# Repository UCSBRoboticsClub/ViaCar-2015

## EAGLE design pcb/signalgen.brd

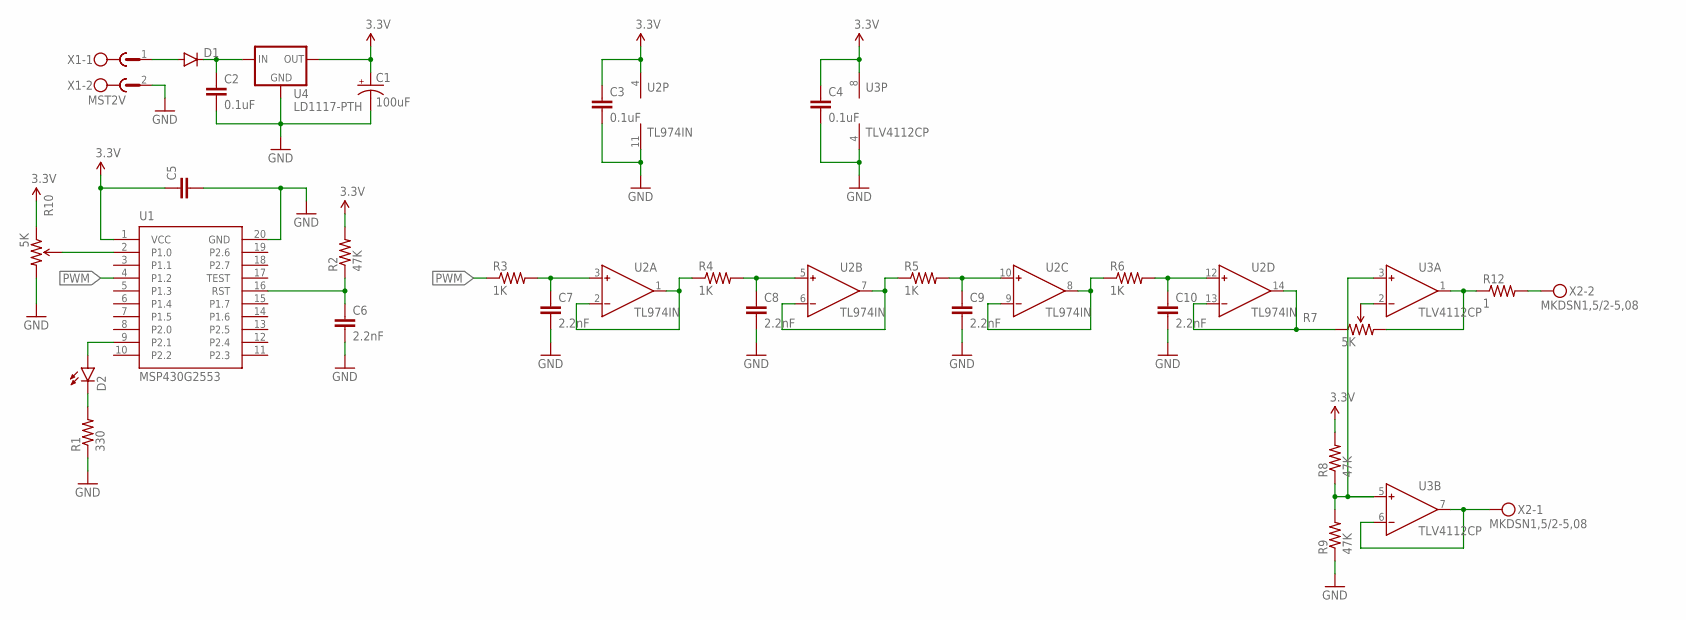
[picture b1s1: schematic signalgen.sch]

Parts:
C1: 100uF; CPOL-RADIAL-100UF-25V
C2, C3, C4: 0.1uF; CAP-PTH-SMALL
C5: CAPPTH; CAP-PTH-SMALL
C6, C7, C8, C9, C10: 2.2nF; CAP-PTH-SMALL
D1: DIODEPTH; DIODE-1N4001
D2: LED-3MM-NO_SILK; LED3MM-NS
R1: 330; AXIAL-0.1
R2, R8, R9: 47K; AXIAL-0.3
R3, R5: 1K; AXIAL-0.1
R4, R6: 1K; AXIAL-0.3
R7, R10: 5K; TRIM_POT_PTH
R12: 1; AXIAL-0.6
U1: MSP430G2553; DIP-20
U2: TL974IN; DIP-14
U3: TLV4112CP; DIP-8
U4: LD1117-PTH; TO-220ABS
X1: MST2V; MSTBV2
X2: MKDSN1,5/2-5,08

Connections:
3.3V: C1.1 (+), C3.1, C4.1, C5.1, R2.P$2 (2), R8.P$2 (2), R10.1 (CCW), U1.1 (VCC), U2.4 (V+), U3.8 (V+), U4.2 (OUT)
GND: C1.2 (-), C2.2, C3.2, C4.2, C5.2, C6.2, C7.2, C8.2, C9.2, C10.2, R1.P$1 (1), R9.P$1 (1), R10.3 (CW), U1.20 (GND), U2.11 (V-), U3.4 (V-), U4.1 (GND), X1.2
unnamed: D1.A, X1.1
unnamed: C2.1, D1.C, U4.3 (IN)
unnamed: D2.K (C), R1.P$2 (2)
unnamed: R4.P$1 (1), U2.1 (OUT), U2.2 (IN-)
unnamed: C7.1, R3.P$2 (2), U2.3 (IN+)
unnamed: R5.P$1 (1), U2.6 (IN-), U2.7 (OUT)
unnamed: C6.1, R2.P$1 (1), U1.16 (RST)
unnamed: U3.6 (IN-), U3.7 (OUT), X2.1
unnamed: C8.1, R4.P$2 (2), U2.5 (IN+)
unnamed: C10.1, R6.P$2 (2), U2.12 (IN+)
unnamed: R12.P$2 (2), X2.2
unnamed: C9.1, R5.P$2 (2), U2.10 (IN+)
unnamed: R6.P$1 (1), U2.8 (OUT), U2.9 (IN-)
unnamed: R7.1 (CCW), U2.13 (IN-), U2.14 (OUT)
unnamed: R8.P$1 (1), R9.P$2 (2), U3.3 (IN+), U3.5 (IN+)
unnamed: R7.3 (CW), R12.P$1 (1), U3.1 (OUT)
unnamed: R10.2 (WIPER), U1.2 (P1.0)
unnamed: R7.2 (WIPER), U3.2 (IN-)
unnamed: D2.A, U1.9 (P2.1)
PWM: R3.P$1 (1), U1.4 (P1.2)

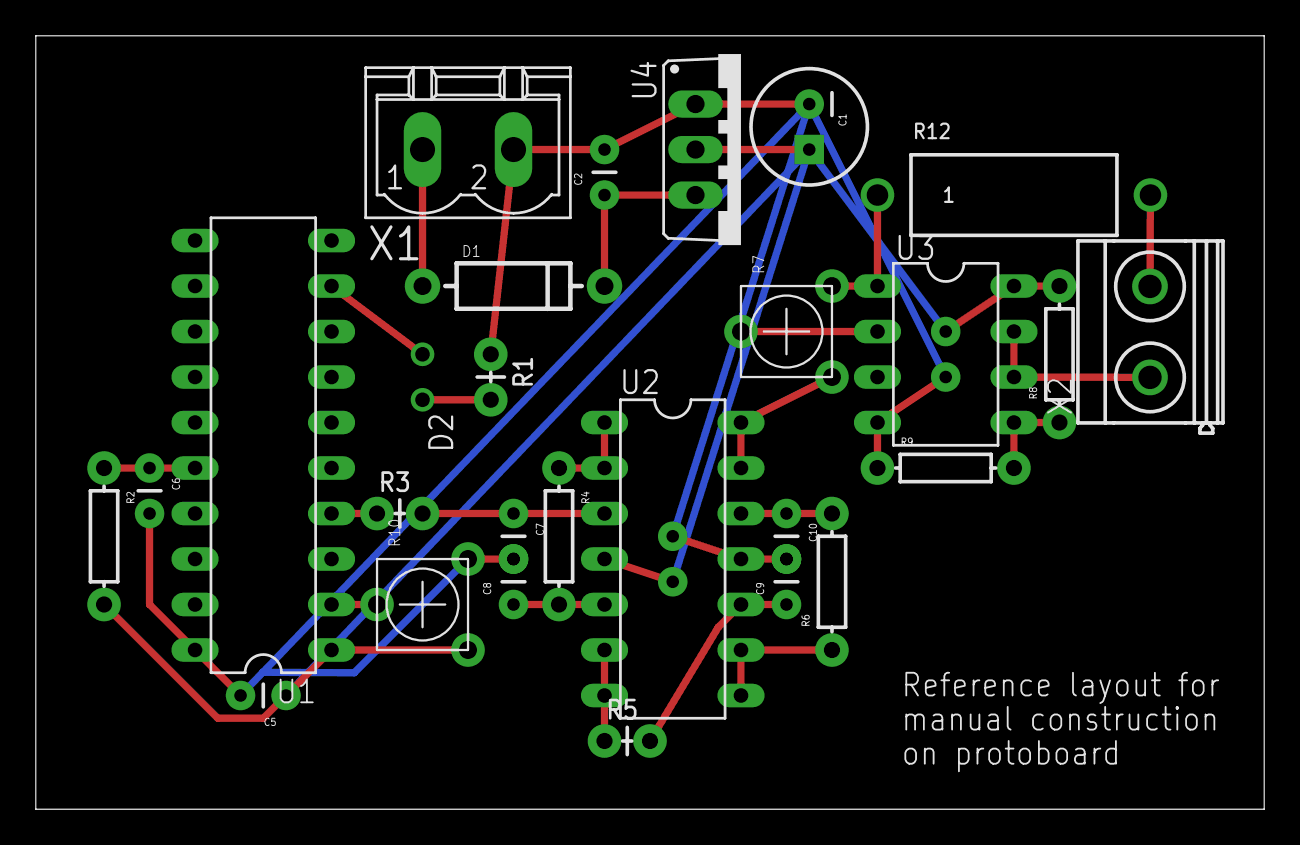
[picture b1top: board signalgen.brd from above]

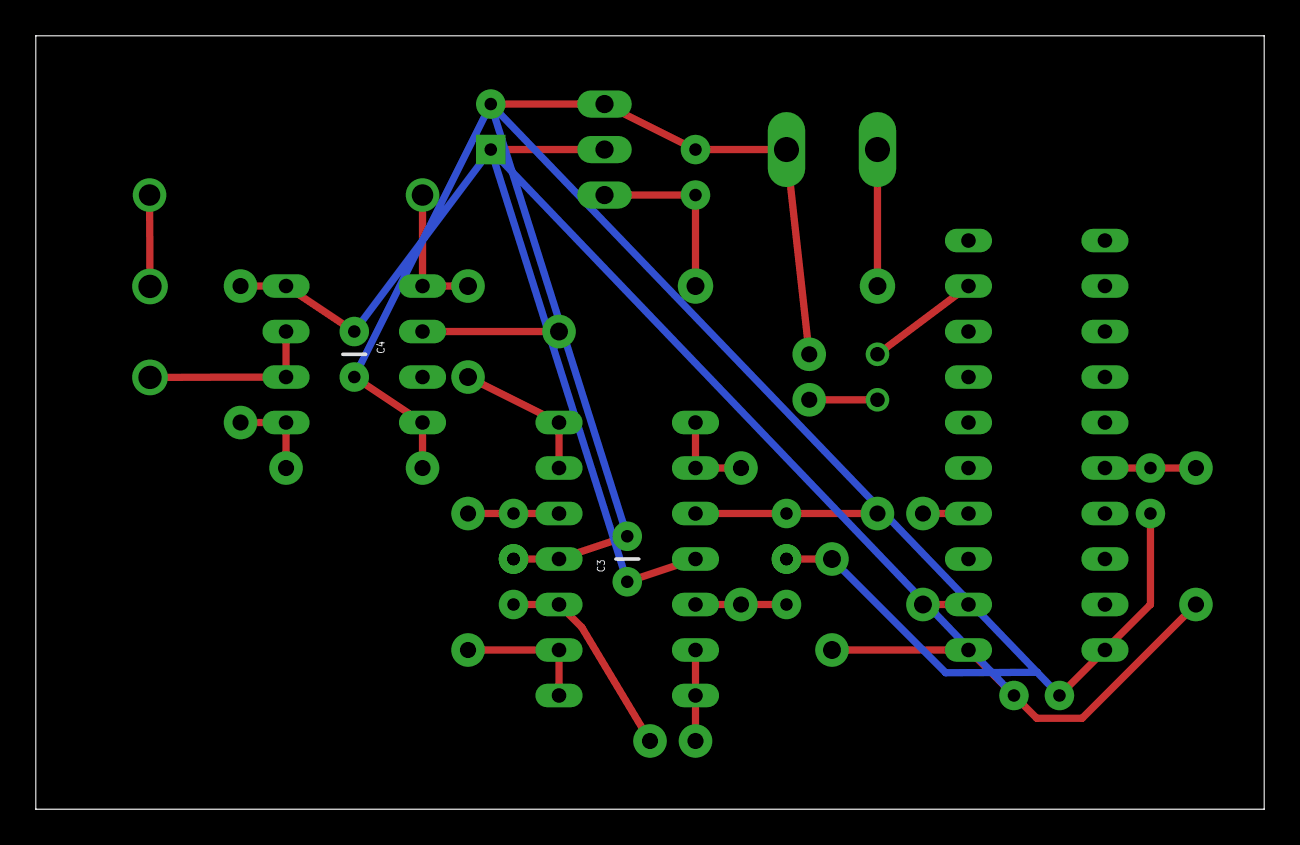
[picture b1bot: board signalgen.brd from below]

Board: 2 copper layers, 68.6 x 43.2 mm, 29 parts (2 on the bottom side), 22 nets.

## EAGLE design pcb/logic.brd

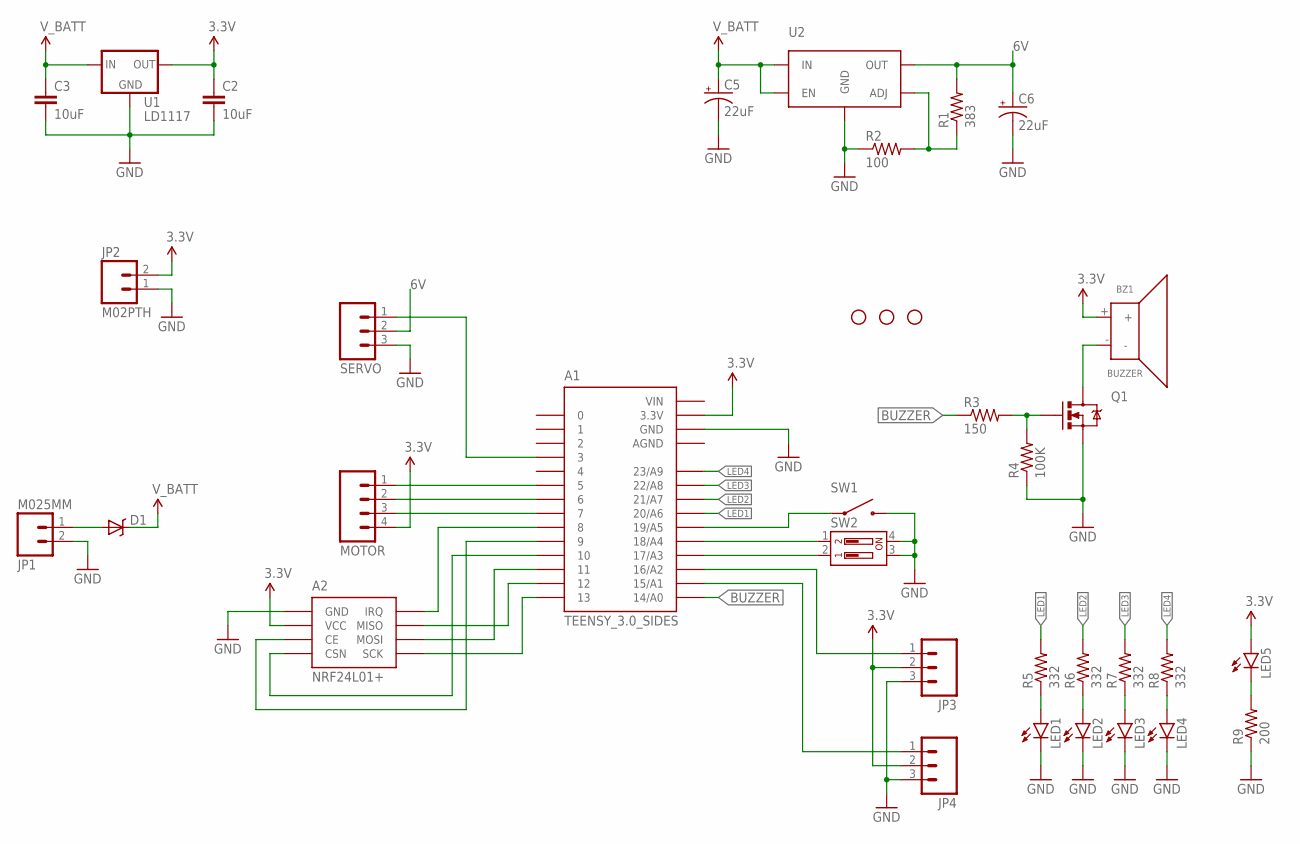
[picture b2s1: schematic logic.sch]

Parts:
A1: TEENSY_3.0_SIDES
A2: NRF24L01+
BZ1: BUZZER
C2, C3: 10uF; 1206
C5, C6: 22uF; CPOL-RADIAL-10UF-25V
D1: DIODE-SCHOTTKY_; SMA-DIODE
JP1: M025MM; SCREWTERMINAL-5MM-2
JP2: M02PTH; 1X02
JP3, JP4: M03LOCK; 1X03_LOCK
LED1, LED2, LED3, LED4, LED5: LED0603; LED-0603
MOTOR: M04LOCK; 1X04_LOCK
Q1: MOSFET-NCHANNELBSS123LT1G; SOT23-3
R1: 383; 0603-RES
R2: 100; 0603-RES
R3: 150; 0603-RES
R4: 100K; 0603-RES
R5, R6, R7, R8: 332; 0603-RES
R9: 200; 0603-RES
SERVO: M03LOCK_LONGPADS; 1X03_LOCK_LONGPADS
STANDOFF1, STANDOFF2, STANDOFF3: STAND-OFF
SW1: FSM4JSMA
SW2: 2-POS-DIPCTS-THRU-HOLE; 209-2LPST
U1: LD1117; SOT-223
U2: MIC29302AWD; TO-252-5

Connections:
3.3V: A1.3.3V, A2.2 (VCC), BZ1.+, C2.1, JP2.2, JP3.2, JP4.2, LED5.A, MOTOR.4, U1.2 (OUT), U1.4 (OUT)
6V: C6.1 (+), R1.2, SERVO.2, U2.P$4 (OUT)
AGND: A1.AGND
BUZZER: A1.14/A0, R3.1
GND: A1.GND, A2.1 (GND), C2.2, C3.2, C5.2 (-), C6.2 (-), JP1.2, JP2.1, JP3.3, JP4.3, LED1.C, LED2.C, LED3.C, LED4.C, Q1.2 (S), R2.1, R4.1, R9.1, SERVO.3, SW1.3 (2), SW1.4 (2), SW2.3, SW2.4, U1.1 (GND), U2.P$3 (GND), U2.PAD (GND)
LED1: A1.20/A6, R5.2
LED2: A1.21/A7, R6.2
LED3: A1.22/A8, R7.2
LED4: A1.23/A9, R8.2
unnamed: D1.A, JP1.1
unnamed: A1.16/A2, JP3.1
unnamed: A1.15/A1, JP4.1
unnamed: R1.1, R2.2, U2.P$5 (ADJ)
unnamed: A1.13, A2.5 (SCK)
unnamed: A1.12, A2.7 (MISO)
unnamed: A1.11, A2.6 (MOSI)
unnamed: A1.10, A2.4 (CSN)
unnamed: A1.8, A2.8 (IRQ)
unnamed: A1.9, A2.3 (CE)
unnamed: A1.3, SERVO.1
unnamed: BZ1.-, Q1.3 (D)
unnamed: Q1.1 (G), R3.2, R4.2
unnamed: LED4.A, R8.1
unnamed: A1.5, MOTOR.1
unnamed: A1.6, MOTOR.2
unnamed: A1.7, MOTOR.3
unnamed: A1.19/A5, SW1.1, SW1.2 (1)
unnamed: A1.18/A4, SW2.1
unnamed: A1.17/A3, SW2.2
unnamed: LED3.A, R7.1
unnamed: LED2.A, R6.1
unnamed: LED1.A, R5.1
unnamed: LED5.C, R9.2
VIN: A1.VIN
V_BATT: C3.1, C5.1 (+), D1.C, U1.3 (IN), U2.P$1 (EN), U2.P$2 (IN)

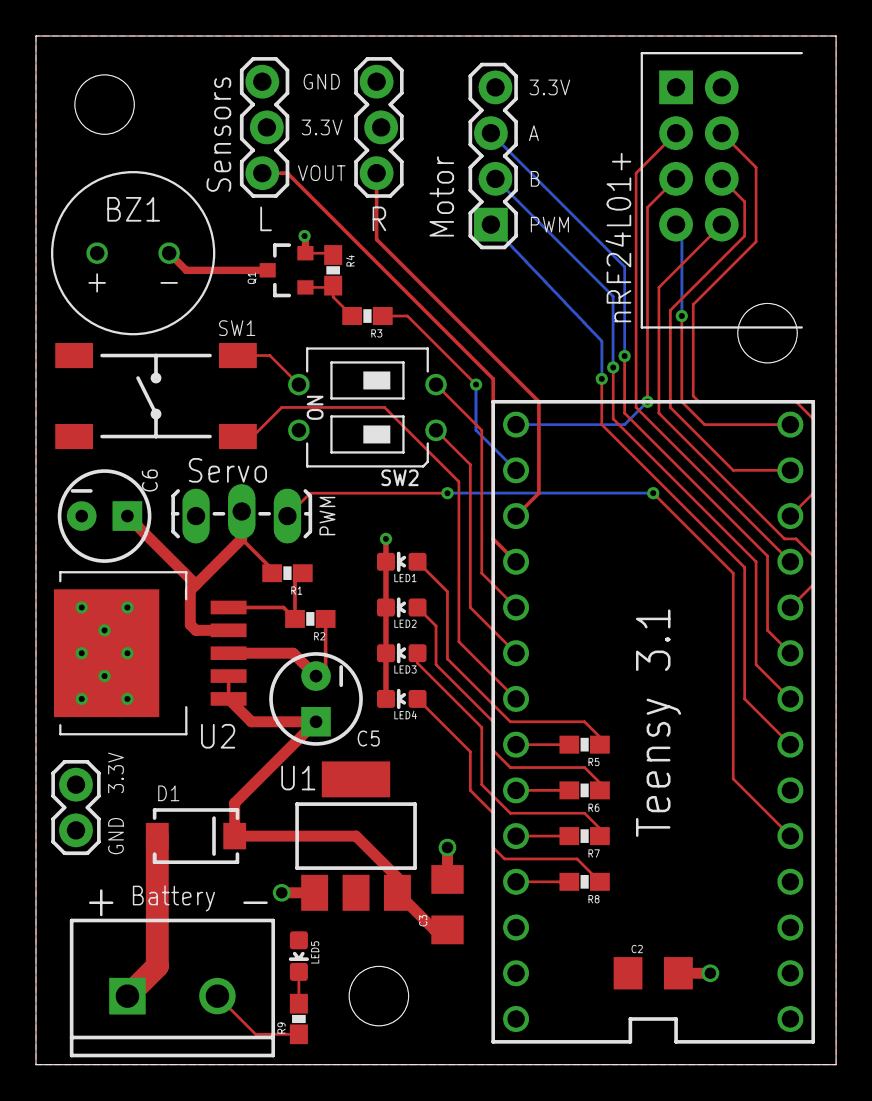
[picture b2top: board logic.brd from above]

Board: 2 copper layers, 44.5 x 57.1 mm, 36 parts (0 on the bottom side), 33 nets.

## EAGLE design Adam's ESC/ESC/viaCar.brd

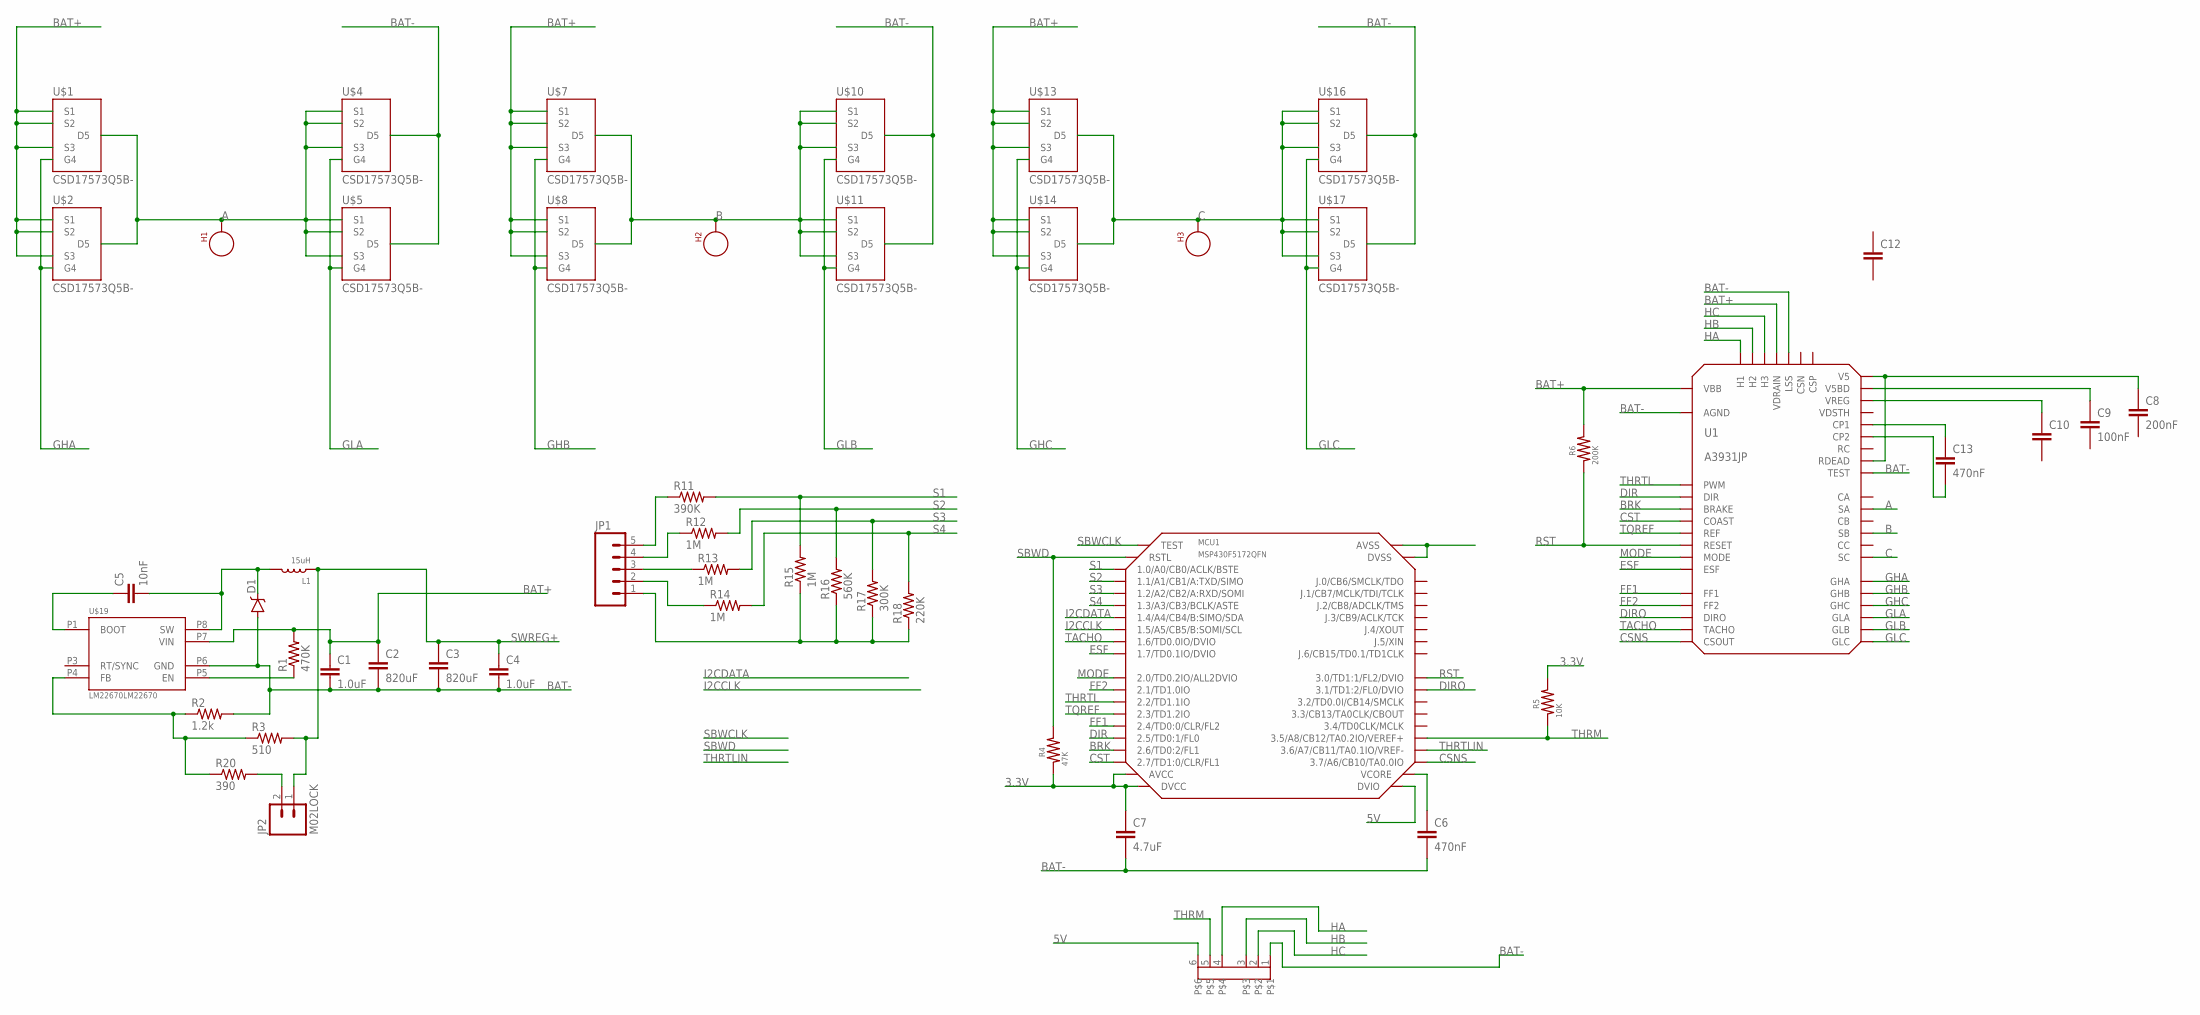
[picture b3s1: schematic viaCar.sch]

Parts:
C1, C4: 1.0uF; 0603-CAP
C2, C3: 820uF; CHEMI-CON_K30_CAPACITOR
C5: 10nF; 0603-CAP
C6, C13: 470nF; 0603
C7: 4.7uF; 0603
C8: 200nF; 0603
C9: 100nF; 0603
C10, C12: 0603CAP-1; 0603
D1: NXPPMEG45A10EPDSCHOTTKY; CFP15
H1, H2, H3: SEW_HOLE; SIMPLE_HOLE
JP1: M05LOCK; 1X05_LOCK
JP2: M02LOCK; 1X02_LOCK
L1: 15uH; WURTH_WE-PD_INDUCTOR
MCU1: MSP430F5172QFN; QFN-40
R1: 470K; 0603-RES
R2: 1.2k; 0603-RES
R3: 510; 0603-RES
R4: 47K; 0603
R5: 10K; 0603
R6: 200K; 0603
R11: 390K; 0603-RES
R12, R13, R14, R15: 1M; 0603-RES
R16: 560K; 0603-RES
R17: 300K; 0603-RES
R18: 220K; 0603-RES
R20: 390; 0603-RES
U1: A3931JP; LQFP-48
U$1, U$2, U$4, U$5, U$7, U$8, U$10, U$11, U$13, U$14, U$16, U$17: CSD17573Q5B-; SON5X6
U$19: LM22670LM22670; POWERPAD8
U$23: JST6X1.5; JST1.5X6

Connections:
3.3V: C7.P$1 (1), MCU1.P27 (DVCC), MCU1.P37 (AVCC), R4.P$1, R5.P$2
5V: MCU1.P17 (DVIO), U$23.6
A: H1.P$1, U1.P31 (SA), U$1.5 (D5), U$2.5 (D5), U$4.1 (S1), U$4.2 (S2), U$4.3 (S3), U$5.1 (S1), U$5.2 (S2), U$5.3 (S3)
B: H2.P$1, U1.P28 (SB), U$7.5 (D5), U$8.5 (D5), U$10.1 (S1), U$10.2 (S2), U$10.3 (S3), U$11.1 (S1), U$11.2 (S2), U$11.3 (S3)
BAT+: C1.1, C2.P$1 (1), R1.2, R6.P$2, U1.P24 (VDRAIN), U1.P45 (VBB), U$1.1 (S1), U$1.2 (S2), U$1.3 (S3), U$2.1 (S1), U$2.2 (S2), U$2.3 (S3), U$7.1 (S1), U$7.2 (S2), U$7.3 (S3), U$8.1 (S1), U$8.2 (S2), U$8.3 (S3), U$13.1 (S1), U$13.2 (S2), U$13.3 (S3), U$14.1 (S1), U$14.2 (S2), U$14.3 (S3), U$19.P7 (VIN)
BAT-: C1.2, C2.P$2 (2), C3.P$2 (2), C4.2, C6.P$2 (2), C7.P$2 (2), D1.P$1 (A), D1.P$2 (A), R2.2, U1.P17 (TEST), U1.P38 (LSS), U1.P41 (AGND), U1.THRM (AGND), U$4.5 (D5), U$5.5 (D5), U$10.5 (D5), U$11.5 (D5), U$16.5 (D5), U$17.5 (D5), U$19.P6 (GND), U$23.1
BRK: U1.P8 (BRAKE)
C: H3.P$1, U1.P25 (SC), U$13.5 (D5), U$14.5 (D5), U$16.1 (S1), U$16.2 (S2), U$16.3 (S3), U$17.1 (S1), U$17.2 (S2), U$17.3 (S3)
CSNS: U1.P19 (CSOUT)
CST: U1.P46 (COAST)
DIR: U1.P9 (DIR)
DIRO: MCU1.P24 (3.1/TD1:2/FL0/DVIO), U1.P44 (DIRO)
ESF: U1.P39 (ESF)
FF1: MCU1.P19 (2.4/TD0:0/CLR/FL2), U1.P6 (FF1)
FF2: MCU1.P14 (2.1/TD1.0IO), U1.P5 (FF2)
GHA: U1.P32 (GHA), U$1.4 (G4), U$2.4 (G4)
GHB: U1.P29 (GHB), U$7.4 (G4), U$8.4 (G4)
GHC: U1.P26 (GHC), U$13.4 (G4), U$14.4 (G4)
GLA: U1.P36 (GLA), U$4.4 (G4), U$5.4 (G4)
GLB: U1.P35 (GLB), U$10.4 (G4), U$11.4 (G4)
GLC: U1.P34 (GLC), U$16.4 (G4), U$17.4 (G4)
HA: U1.P10 (H1), U$23.4
HB: U1.P11 (H2), U$23.3
HC: U1.P12 (H3), U$23.2
I2CCLK: MCU1.P6 (1.5/A5/CB5/B:SOMI/SCL)
I2CDATA: MCU1.P5 (1.4/A4/CB4/B:SIMO/SDA)
MODE: U1.P15 (MODE)
unnamed: C6.P$1 (1), MCU1.P25 (VCORE)
unnamed: C5.2, D1.P$3 (C), L1.P$1, U$19.P8 (SW)
unnamed: C5.1, U$19.P1 (BOOT)
unnamed: MCU1.P18 (DVSS), MCU1.P26 (DVSS), MCU1.P40 (AVSS), MCU1.P$42 (DVSS), MCU1.P$43 (DVSS), MCU1.P$44 (DVSS), MCU1.P$45 (DVSS), MCU1.P$46 (DVSS), MCU1.P$47 (DVSS), MCU1.P$48 (DVSS), MCU1.P$49 (DVSS), MCU1.P$50 (DVSS), MCU1.P$51 (DVSS), MCU1.P$52 (DVSS), MCU1.P$53 (DVSS), MCU1.P$54 (DVSS), MCU1.P$55 (DVSS), MCU1.P$56 (DVSS), MCU1.P$57 (DVSS), MCU1.P$58 (DVSS), MCU1.P$59 (DVSS), MCU1.P$60 (DVSS), MCU1.P$61 (DVSS), MCU1.P$62 (DVSS), MCU1.P$63 (DVSS), MCU1.P$64 (DVSS), MCU1.P$65 (DVSS), MCU1.P$66 (DVSS), MCU1.THRM (DVSS)
unnamed: C8.P$1 (1), U1.P4 (V5), U1.P18 (RDEAD)
unnamed: R1.1, U$19.P5 (EN)
unnamed: R2.1, R3.1, R20.1, U$19.P4 (FB)
unnamed: C9.P$1 (1), U1.P3 (V5BD)
unnamed: C10.P$1 (1), U1.P40 (VREG)
unnamed: C13.P$1 (1), U1.P42 (CP1)
unnamed: C13.P$2 (2), U1.P43 (CP2)
unnamed: JP1.5, R11.1
unnamed: JP1.4, R12.1
unnamed: JP1.3, R13.1
unnamed: JP1.2, R14.1
unnamed: JP2.2, R20.2
unnamed: JP1.1, R15.1, R16.1, R17.1, R18.1
RST: R6.P$1, U1.P2 (RESET)
S1: MCU1.P1 (1.0/A0/CB0/ACLK/BSTE), R11.2, R15.2
S2: MCU1.P2 (1.1/A1/CB1/A:TXD/SIMO), R12.2, R16.2
S3: MCU1.P3 (1.2/A2/CB2/A:RXD/SOMI), R13.2, R17.2
S4: MCU1.P4 (1.3/A3/CB3/BCLK/ASTE), R14.2, R18.2
SBWCLK: MCU1.P32 (TEST)
SBWD: MCU1.P33 (RSTL), R4.P$2
SWREG+: C3.P$1 (1), C4.1, JP2.1, L1.P$2, R3.2
TACHO: MCU1.P11 (1.6/TD0.0IO/DVIO), U1.P7 (TACHO)
THRM: MCU1.P34 (3.5/A8/CB12/TA0.2IO/VEREF+), R5.P$1, U$23.5
THRTL: U1.P14 (PWM)
THRTLIN: MCU1.P35 (3.6/A7/CB11/TA0.1IO/VREF-)
TQREF: MCU1.P16 (2.3/TD1.2IO), U1.P20 (REF)

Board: 2 copper layers, 50 parts (0 on the bottom side), 46 nets, no tracks yet.

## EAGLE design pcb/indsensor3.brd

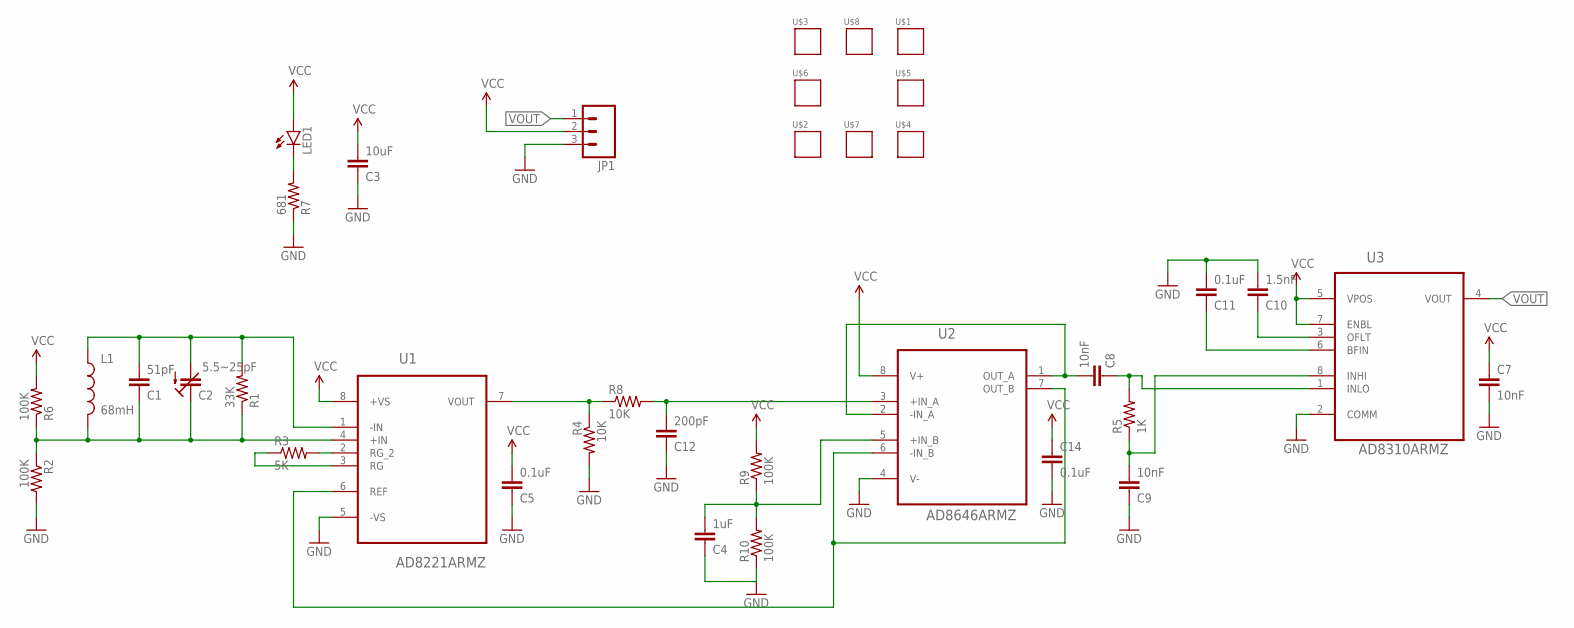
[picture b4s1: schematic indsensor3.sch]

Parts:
C1: 51pF; 0603-CAP
C2: 5.5~25pF; TRIMCAP-TZY
C3: 10uF; 1206
C4: 1uF; 0603-CAP
C5, C11, C14: 0.1uF; 0603-CAP
C7, C8, C9: 10nF; 0603-CAP
C10: 1.5nF; 0603-CAP
C12: 200pF; 0603-CAP
JP1: M03LOCK; 1X03_LOCK
L1: 68mH; RLB0912
LED1: LED0603; LED-0603
R1: 33K; 0603-RES
R2, R6, R9, R10: 100K; 0603-RES
R3: 5K; 0603-RES
R4, R8: 10K; 0603-RES
R5: 1K; 0603-RES
R7: 681; 0603-RES
U1: AD8221ARMZ; SOP65P490X110-8N
U2: AD8646ARMZ; SOP65P490X110-8N
U3: AD8310ARMZ; SOP65P490X110-8N
U$1, U$2, U$3, U$4: SHIELD-CORNER
U$5, U$6: SHIELD-MIDDLE
U$7: SHIELD-MIDDLEPART
U$8: SHIELD-MIDDLE3

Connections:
10NF: R4.1, R8.1, U1.7 (VOUT)
GND: C3.1, C4.1, C5.1, C7.2, C9.1, C10.2, C11.2, C12.1, C14.2, JP1.3, R2.2, R4.2, R7.1, R10.1, U1.5 (-VS), U2.4 (V-), U3.2 (COMM)
unnamed: R3.2, U1.2 (RG_2)
unnamed: R3.1, U1.3 (RG)
unnamed: C10.1, U3.3 (OFLT)
unnamed: C8.1, R5.2, U3.1 (INLO)
unnamed: C9.2, R5.1, U3.8 (INHI)
unnamed: LED1.C, R7.2
unnamed: C1.1, C2.2 (E), L1.2, R1.1, R2.1, R6.1, U1.4 (+IN)
unnamed: C11.1, U3.6 (BFIN)
unnamed: C8.2, U2.1 (OUT_A), U2.2 (-IN_A)
unnamed: C1.2, C2.1 (A), L1.1, R1.2, U1.1 (-IN)
unnamed: C12.2, R8.2, U2.3 (+IN_A)
unnamed: U1.6 (REF), U2.6 (-IN_B), U2.7 (OUT_B)
unnamed: C4.2, R9.1, R10.2, U2.5 (+IN_B)
VCC: C3.2, C5.2, C7.1, C14.1, JP1.2, LED1.A, R6.2, R9.2, U1.8 (+VS), U2.8 (V+), U3.5 (VPOS), U3.7 (ENBL)
VOUT: JP1.1, U3.4 (VOUT)

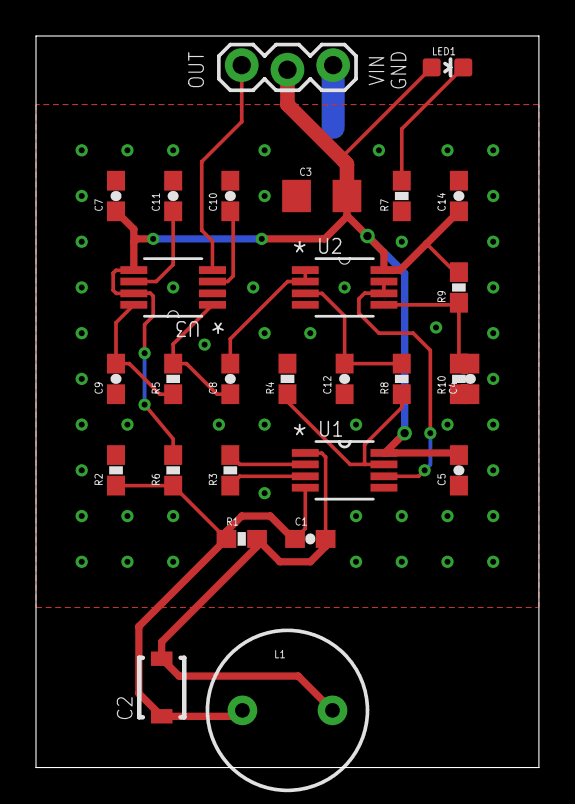
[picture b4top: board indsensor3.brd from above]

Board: 2 copper layers, 27.9 x 40.6 mm, 36 parts (0 on the bottom side), 17 nets.

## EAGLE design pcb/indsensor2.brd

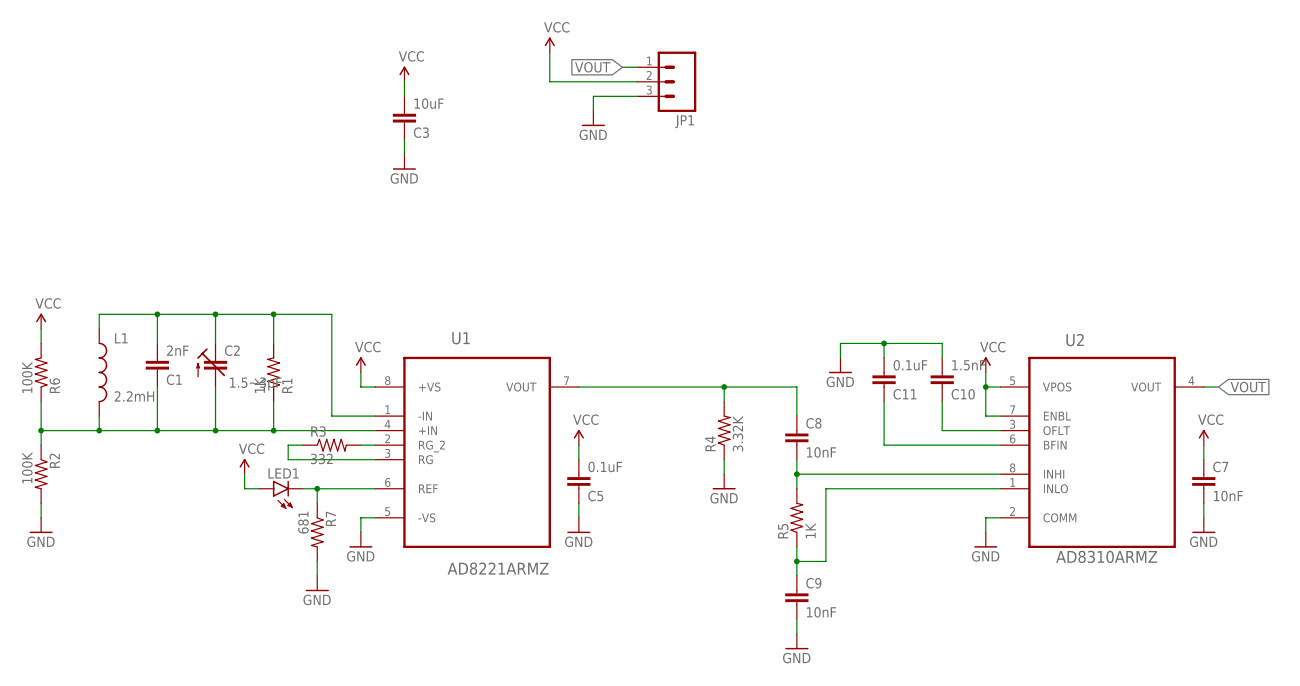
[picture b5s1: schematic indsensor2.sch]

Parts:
C1: 2nF; 0603-CAP
C2: 1.5~3pF; TRIMCAP-TZY
C3: 10uF; 0603-CAP
C5, C11: 0.1uF; 0603-CAP
C7, C8, C9: 10nF; 0603-CAP
C10: 1.5nF; 0603-CAP
JP1: M03LOCK; 1X03_LOCK
L1: 2.2mH; 1812
LED1: LED0603; LED-0603
R1, R5: 1K; 0603-RES
R2, R6: 100K; 0603-RES
R3: 332; 0603-RES
R4: 3.32K; 0603-RES
R7: 681; 0603-RES
U1: AD8221ARMZ; SOP65P490X110-8N
U2: AD8310ARMZ; SOP65P490X110-8N

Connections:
10NF: C8.1, R4.2, U1.7 (VOUT)
GND: C3.1, C5.1, C7.2, C9.2, C10.2, C11.2, JP1.3, R2.2, R4.1, R7.2, U1.5 (-VS), U2.2 (COMM)
unnamed: R3.2, U1.2 (RG_2)
unnamed: R3.1, U1.3 (RG)
unnamed: C10.1, U2.3 (OFLT)
unnamed: C8.2, R5.2, U2.8 (INHI)
unnamed: C9.1, R5.1, U2.1 (INLO)
unnamed: LED1.C, R7.1, U1.6 (REF)
unnamed: C1.2, C2.2 (E), L1.1, R1.2, U1.1 (-IN)
unnamed: C11.1, U2.6 (BFIN)
unnamed: C1.1, C2.1 (A), L1.2, R1.1, R2.1, R6.1, U1.4 (+IN)
VCC: C3.2, C5.2, C7.1, JP1.2, LED1.A, R6.2, U1.8 (+VS), U2.5 (VPOS), U2.7 (ENBL)
VOUT: JP1.1, U2.4 (VOUT)

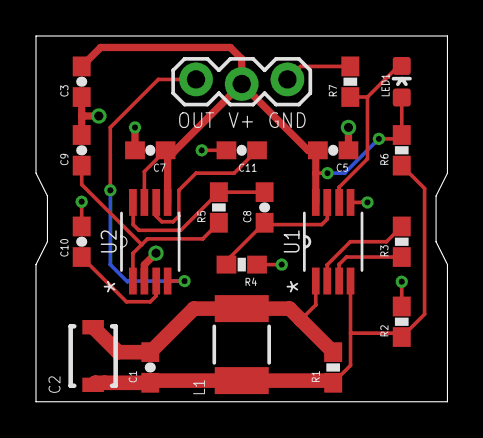
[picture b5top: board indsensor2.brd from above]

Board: 2 copper layers, 22.9 x 20.3 mm, 21 parts (0 on the bottom side), 13 nets.

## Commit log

2015-02-06 Added inductive sensor PCB files
2015-02-15 Updated component values
2015-03-13 Imported code from micromouse-2015 and viacar-2014
2015-03-13 Fixed build
2015-03-13 ESC Upload
    esc work thus far.
2015-03-13 viacar2014.ino
    the code i was changing 3-6
2015-03-13 Updated code
2015-03-14 Added datasheets
2015-03-14 Line sensing seems to work
2015-03-14 Variable setting over the terminal is more versatile
2015-03-14 Added PID controller for servo
2015-03-24 Added new logic board
2015-03-24 Minor changes to board
2015-03-26 Fixed resistor values
2015-03-26 Added regulator datasheet
2015-04-05 Changed gain resistor
2015-04-05 Added signal generator schematic and layout
2015-04-05 Added sensor bracket v1 STL file
2015-04-07 Updated resistor values
2015-04-07 Added new sensor bracket
2015-04-07 Updated code for new board
2015-04-07 Fixed radio pins for new board
2015-04-07 Changed blinkenlights
2015-04-08 Updates from initial testing
2015-04-08 Changed out of range behavior
2015-04-10 Made cad folder and added the flag mounting bracket
2015-04-11 Added a taper to the inside of the shaft hole
2015-04-11 Implemented system linearization
2015-04-11 ADC library is now included with teensyduio 1.22
2015-04-11 Changed position score weighting
2015-04-11 Use a lowpass for velocity estimation
2015-04-12 Modulate speed using estimated angle
2015-04-13 Controller is no longer time/speed dependant
2015-04-15 Updates from tuesday testing
2015-04-17 Changes from tuesday testing
2015-04-18 Changed command macros
2015-04-18 Changed size of Flag holder
    Increaded flag shaft size and increased size for strength
2015-04-18 Changed flag mount to increase strength and improve fit
2015-04-18 Wheel encoder and more
2015-04-18 Made Ruler Bracket
2015-04-19 Relaxed Kd, boosted speed

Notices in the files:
parts and their libraries:
SparkFun-Capacitors: Licensing: Creative Commons ShareAlike 4.0 International - https://creativecommons.org/licenses/by-sa/4.0
SparkFun-DiscreteSemi: Licensing: CC v3.0 Share-Alike You are welcome to use this library for commercial purposes.
